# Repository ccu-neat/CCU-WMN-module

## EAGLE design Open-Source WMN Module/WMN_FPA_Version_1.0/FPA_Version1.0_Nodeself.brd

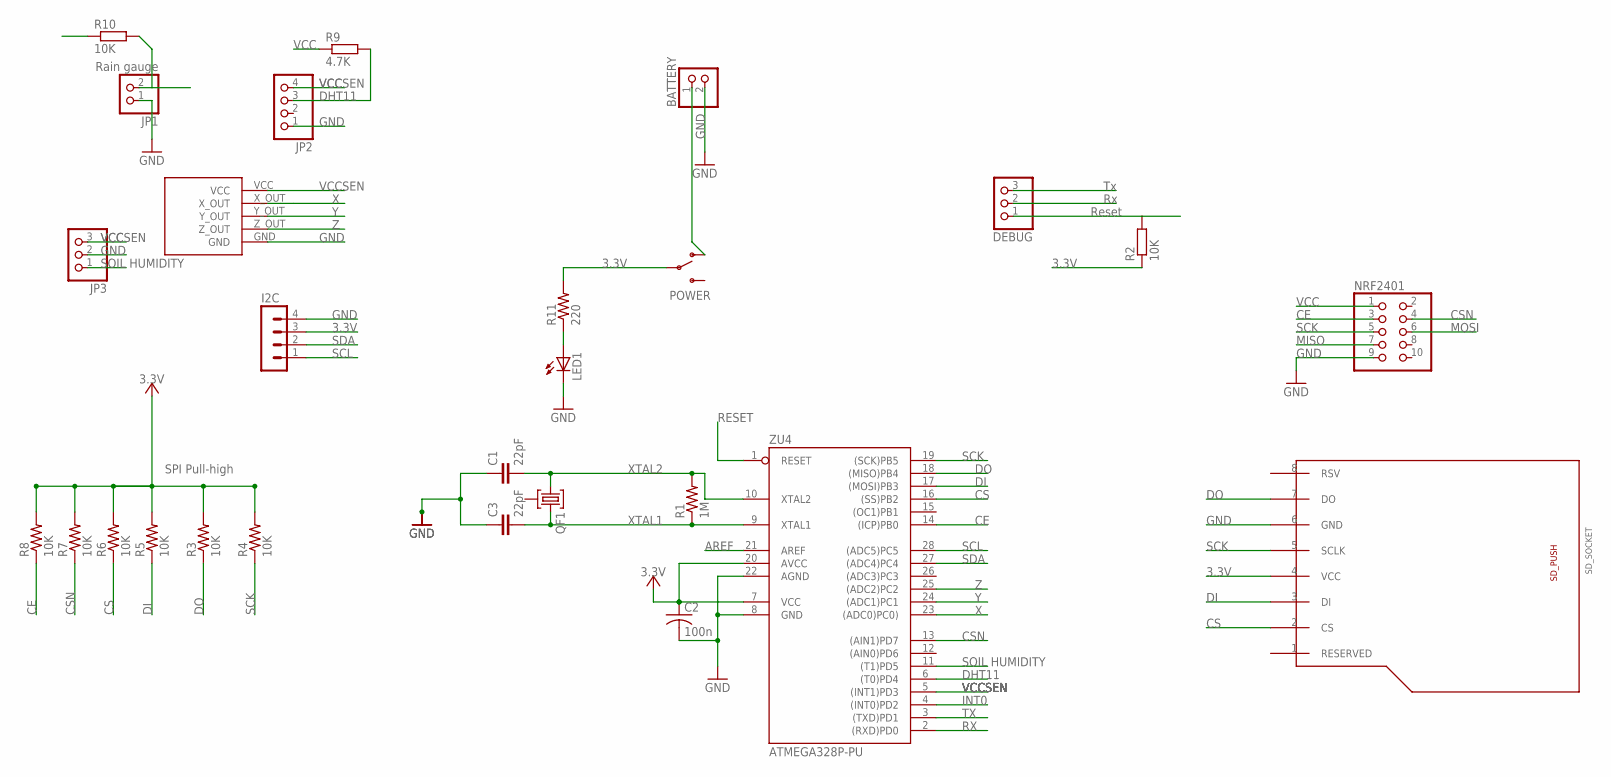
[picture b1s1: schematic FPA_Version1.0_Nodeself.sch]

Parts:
BATTERY: PINHD-1X2; 1X02
C1, C3: 22pF; C0805
C2: 100n; C1206
DEBUG: PINHD-1X3; 1X03
I2C: MA04-1
JP1: Rain gauge; 1X02
JP2: PINHD-1X4; 1X04
JP3: PINHD-1X3; 1X03
LED1: LED_E; LED_1206
NRF2401: PINHD-2X5; 2X05
POWER: SWITCH-SPSTPTH; SWITCH-SPDT
QF1: 10M8AHC49U; HC49U
R1: 1M; 1206
R2: 10K; R1206
R3, R4, R5, R6, R7, R8: 10K; R0805
R9: 4.7K; M1206
R10: 10K; M1206
R11: 220; 1206
SD_SOCKET: SD_CARD_SOCKET
U$2: GY-61
ZU4: ATMEGA328P-PU; DIL28-3

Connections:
3.3V: C2.1, I2C.3, NRF2401.1, POWER.2, R2.1, R3.2, R4.2, R5.2, R6.2, R7.2, R8.2, R9.1, R10.1, R11.2, SD_SOCKET.4 (VCC), ZU4.7 (VCC), ZU4.20 (AVCC)
AREF: ZU4.21 (AREF)
CE: NRF2401.3, R8.1, ZU4.14 ((ICP)PB0)
CSN: NRF2401.4, R7.1, ZU4.13 ((AIN1)PD7)
GND: BATTERY.2, C1.1, C2.2, C3.1, I2C.4, JP1.1, JP2.1, JP3.2, LED1.C, NRF2401.9, SD_SOCKET.6 (GND), U$2.GND, ZU4.8 (GND), ZU4.22 (AGND)
HRX: DEBUG.2, ZU4.3 ((TXD)PD1)
HTX: DEBUG.3, ZU4.2 ((RXD)PD0)
INT0: JP1.2, R10.2, ZU4.4 ((INT0)PD2)
MISO: NRF2401.7, R3.1, SD_SOCKET.7 (DO), ZU4.18 ((MISO)PB4)
MOSI: NRF2401.6, R5.1, SD_SOCKET.3 (DI), ZU4.17 ((MOSI)PB3)
unnamed: BATTERY.1, POWER.1 (O)
unnamed: LED1.A, R11.1
RESET: DEBUG.1, R2.2, ZU4.1 (RESET)
SCK: NRF2401.5, R4.1, SD_SOCKET.5 (SCLK), ZU4.19 ((SCK)PB5)
SCL: I2C.1, ZU4.28 ((ADC5)PC5)
SDA: I2C.2, ZU4.27 ((ADC4)PC4)
SS: R6.1, SD_SOCKET.2 (CS), ZU4.16 ((SS)PB2)
T0: JP2.3, R9.2, ZU4.6 ((T0)PD4)
T1: JP3.1, ZU4.11 ((T1)PD5)
VCCSEN: JP2.4, JP3.3, U$2.VCC, ZU4.5 ((INT1)PD3)
X: U$2.X_OUT, ZU4.23 ((ADC0)PC0))
XTAL1: C3.2, QF1.3, R1.1, ZU4.9 (XTAL1)
XTAL2: C1.2, QF1.1, R1.2, ZU4.10 (XTAL2)
Y: U$2.Y_OUT, ZU4.24 ((ADC1)PC1)
Z: U$2.Z_OUT, ZU4.25 ((ADC2)PC2)

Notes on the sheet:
GND
SCK
3.3V
VCC
MISO
CSN
MOSI
Reset
SPI Pull-high
INT0
RESET
SDA
SCL
DHT11
SOIL HUMIDITY

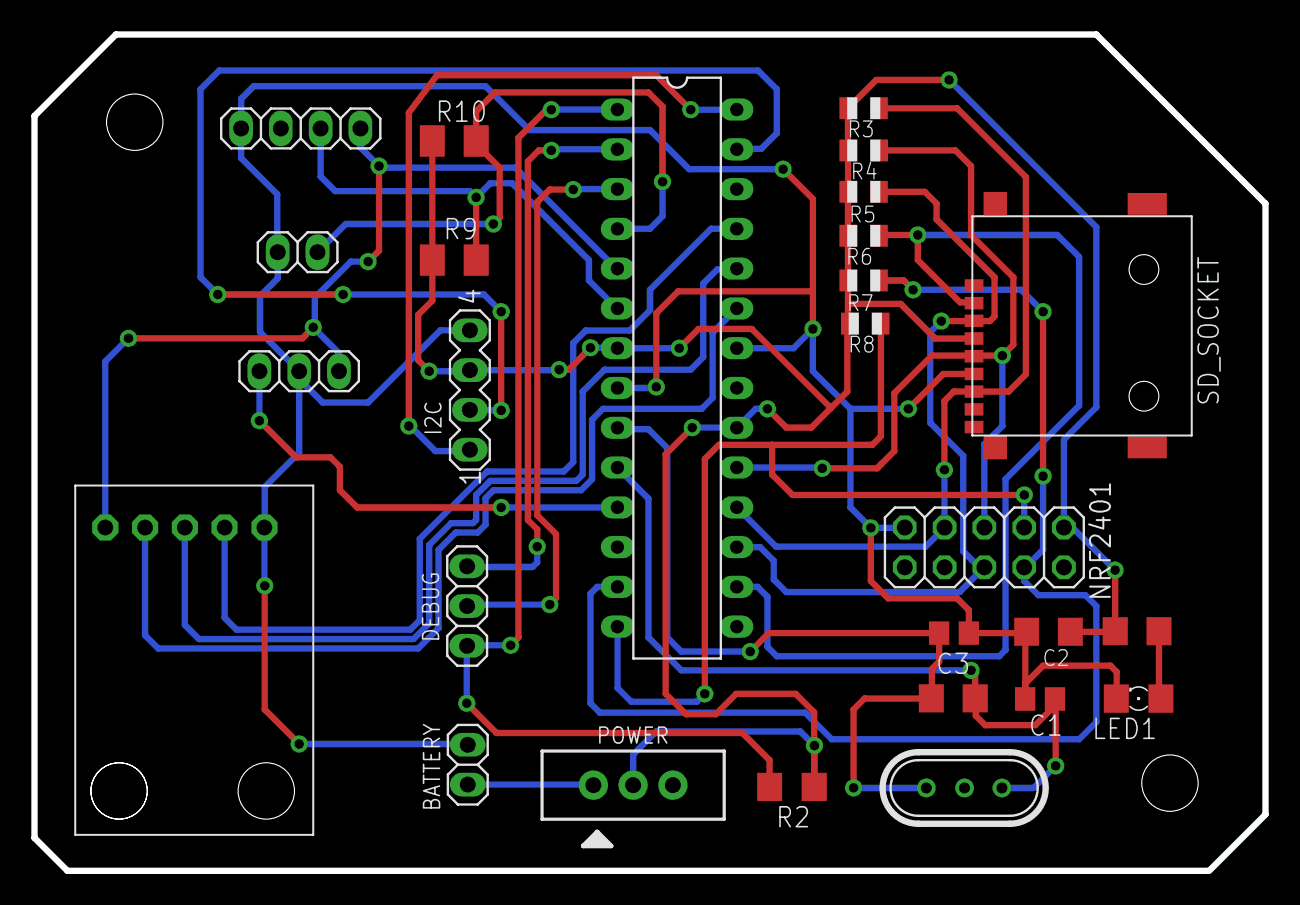
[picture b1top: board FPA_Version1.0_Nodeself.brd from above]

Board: 2 copper layers, 78.6 x 53.4 mm, 27 parts (0 on the bottom side), 24 nets.

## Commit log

2015-05-04 CCU Open-Source Wireless Mesh Network Module
